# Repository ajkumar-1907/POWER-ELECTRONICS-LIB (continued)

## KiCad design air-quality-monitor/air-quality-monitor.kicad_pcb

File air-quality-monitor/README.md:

# IoT Air Quality Monitoring System

A battery-powered, Wi-Fi connected air-quality monitor built around an **ESP-12E (ESP8266)** and an **MQ-135** gas sensor. It reads gas concentration, shows it on an SSD1306 OLED, and can send the data over Wi-Fi. The board has its own USB-C programming interface, a Li-ion charger and power regulation.

### 3D views

### Layer views

| Front copper | Back copper |
|---|---|
|  |  |
| **Front silkscreen** | **Back silkscreen** |
|  |  |

## Overview

The board combines six functional blocks on one 2-layer PCB:

| Block | Parts | Function |
|---|---|---|
| **USB-to-UART** | USB-C (J23), CH340C (U7), SS8050 ×2 (Q3, Q4) | Programming and serial monitor over USB-C, with ESP auto-reset/flash |
| **MCU** | ESP-12E (U1), RST and FLASH buttons | Wi-Fi microcontroller; reads the sensor and drives the display |
| **Gas sensor** | MQ-135 (U2) + load/divider resistors | Analog gas reading into the ESP8266 ADC (A0) |
| **Display** | 4-pin header (J2) | SSD1306 128×64 I²C OLED (GND / 5V / SCL / SDA) |
| **Battery charging** | TP4056 (U5), status LEDs D1/D2 | Single-cell Li-ion charging from USB |
| **Power supply** | MT3608 boost (U4) + AMS1117-3.3 (U6) | Battery → 5 V (sensor heater, OLED) → 3.3 V (ESP-12E) |

## Working Principle

1. **Power path:** USB-C supplies 5 V. The CC pins have 5.1 kΩ pull-downs (R6, R7), so a USB-C host provides power, and TVS diodes (D6, D7, D9) protect the USB lines. The TP4056 charges the Li-ion cell on J1 at about 1 A (set by R13 = 1.2 kΩ). The red and green LEDs show charging and done.
2. **5 V rail:** the MT3608 boosts the battery voltage (3.0–4.2 V) to 5 V through L1 and Schottky diode D10. USB 5 V is OR-ed onto the same rail through D8 (SS34), so the board runs from USB or from battery.
3. **3.3 V rail:** the AMS1117-3.3 LDO powers the ESP-12E from the 5 V rail.
4. **Sensing:** the MQ-135's heater runs from 5 V. Its sensing element forms a divider with the load resistors, and the scaled voltage goes to the ESP8266's ADC pin. The resistance falls as pollutant gas concentration rises (NH₃, NOₓ, alcohol, benzene, smoke, CO₂).
5. **Programming:** the CH340C converts USB to UART. Its DTR and RTS lines drive the classic two-transistor (Q3, Q4) circuit that pulls the ESP's RESET and GPIO0, so uploads from the Arduino IDE or esptool need no button presses. Manual RST and FLASH buttons are also provided.
6. **Display and I/O:** the OLED connects over I²C (SDA/SCL on J2). D3 is a status LED on GPIO14.

## Key Equations

**TP4056 charge current:**
```
I_charge = 1200 / R_PROG = 1200 / 1.2 kΩ ≈ 1 A
```

**MT3608 boost output (V_FB = 0.6 V):**
```
Vout = 0.6 V × (1 + R_top / R_bottom)      for 5 V: R_top / R_bottom ≈ 7.33
```

**MQ-135 sensor resistance from the measured voltage:**
```
Rs = R_L × (Vc − V_out) / V_out          ppm ≈ a × (Rs / R0)^b   (calibrated curve)
```

**ESP8266 ADC input (0–1 V full scale on ESP-12E A0):**
```
V_ADC = V_sensor × R_bottom / (R_top + R_bottom)   →  must stay ≤ 1.0 V
```

## Typical Applications

- Indoor air-quality monitoring for homes, classrooms and offices
- Kitchen and garage smoke or gas alerts
- IoT dashboards (Blynk, ThingSpeak, MQTT / Home Assistant)
- Learning platform for ESP8266, sensors and battery-powered design

## Specifications (this design)

| Parameter | Value |
|---|---|
| MCU | ESP-12E (ESP8266, 2.4 GHz Wi-Fi) |
| Sensor | MQ-135 (analog) |
| Display | SSD1306 128×64 OLED, I²C |
| Power Input | USB-C 5 V |
| Battery | 1-cell Li-ion / Li-Po (JST-PH 2-pin), 1 A charging |
| Rails | 5 V (MT3608 boost / USB) and 3.3 V (AMS1117) |
| USB-UART | CH340C with auto-reset / auto-flash |
| Board Size | 68 × 47.4 mm, 2-layer, antenna keep-out cut-out |

## Bill of Materials

The full BOM is in [`bom.csv`](bom.csv). The main parts are:

| Ref | Value | Package |
|---|---|---|
| U1 | ESP-12E | Module |
| U2 | MQ-135 gas sensor | 6-pin |
| U4 | MT3608 boost converter | SOT-23-6 |
| U5 | TP4056 Li-ion charger | ESOP-8 |
| U6 | AMS1117-3.3 LDO | SOT-223 |
| U7 | CH340C USB-UART | SOIC-16 |
| Q3, Q4 | SS8050 NPN | SOT-23 |
| D8, D10 | SS34 Schottky | SMA |
| D6, D7, D9 | LESD5D5.0CT1G TVS | SOD-523 |
| J23 | USB-C receptacle, 16-pin | SMD |
| J1 / J2 / J3 | JST-PH battery / OLED header / 3-pin header | THT |

## Design Notes

- **MT3608 parts not specified.** R1, R2 (feedback divider) and L1 are left as "R" and "L" in the schematic. Pick R_top / R_bottom ≈ 7.33 for 5 V (for example 22 kΩ / 3 kΩ) and a 22 µH power inductor rated above about 2 A before ordering.
- **ADC range.** The ESP-12E's A0 pin reads 0–1 V. Check that the sensor divider keeps the maximum reading under 1 V.
- **Sensor warm-up and power.** The MQ-135 heater draws about 150 mA at 5 V and needs a 24–48 h burn-in plus calibration (R0 in clean air) before readings are meaningful. On battery it is the dominant load, so consider duty-cycling the heater or deep sleep for long runtime.
- **Antenna.** Keep the cut-out and keep-out zone under the ESP-12E antenna free of copper and components for good Wi-Fi range.
- **Firmware** isn't included in this folder. The 3D models used for the renders (OLED, sensor, USB-C, etc.) aren't included either; KiCad shows those parts without a 3D body.

## Pros & Cons

**Pros:**
- All-in-one: MCU, sensor, display, charger and programmer on a single board
- USB-C with ESD protection and one-click auto-flash
- Runs from USB or battery (power OR-ing)
- Wi-Fi connectivity for cloud dashboards

**Cons:**
- MQ-135 is a low-cost, broad-spectrum sensor: it is not selective and needs calibration
- The heater current limits battery life
- The AMS1117 LDO is inefficient from 5 V
- The ESP8266 has only one ADC channel (0–1 V)

## Files in This Folder

| File | Description |
|---|---|
| `air-quality-monitor.kicad_pro` | KiCad project file |
| `air-quality-monitor.kicad_sch` | Schematic source file |
| `air-quality-monitor.kicad_pcb` | PCB layout source file |
| `air-quality-monitor-PTH.drl` | Plated through-hole drill file (incl. USB-C shell slots) |
| `air-quality-monitor-NPTH.drl` | Non-plated drill file |
| `gerbers/` | Gerber files for fabrication (incl. paste layers for stencil) |
| `bom.csv` | Bill of materials |
| `schematic.png` | Schematic image |
| `pcb-layout2.png` | PCB layout preview (KiCad editor view) |
| `pcb-layout.png` | PCB top and bottom render from the Gerbers |
| `pcb-front-copper.png` / `pcb-back-copper.png` | Copper layer views |
| `pcb-front-silkscreen.png` / `pcb-back-silkscreen.png` | Silkscreen layer views |
| `pcb-3d-top.png` / `pcb-3d-bottom.png` / `pcb-3d-angle.png` | 3D renders |

## How to Use

1. Clone or download this repository.
2. Open `air-quality-monitor.kicad_pro` in [KiCad](https://www.kicad.org/) (v10 or later).
3. Set values for R1, R2 and L1 (see Design Notes), then order the PCB: zip the contents of `gerbers/` together with the two `.drl` files and upload them to any fab.
4. After assembly, plug in USB-C. The board shows up as a CH340 COM port. Flash it from the Arduino IDE (board: *NodeMCU 1.0 (ESP-12E)*) or with esptool.
5. Connect the OLED to J2 and a 1-cell Li-ion battery to J1, then let the MQ-135 burn in before calibrating.

## License

Released under the [MIT License](../LICENSE).

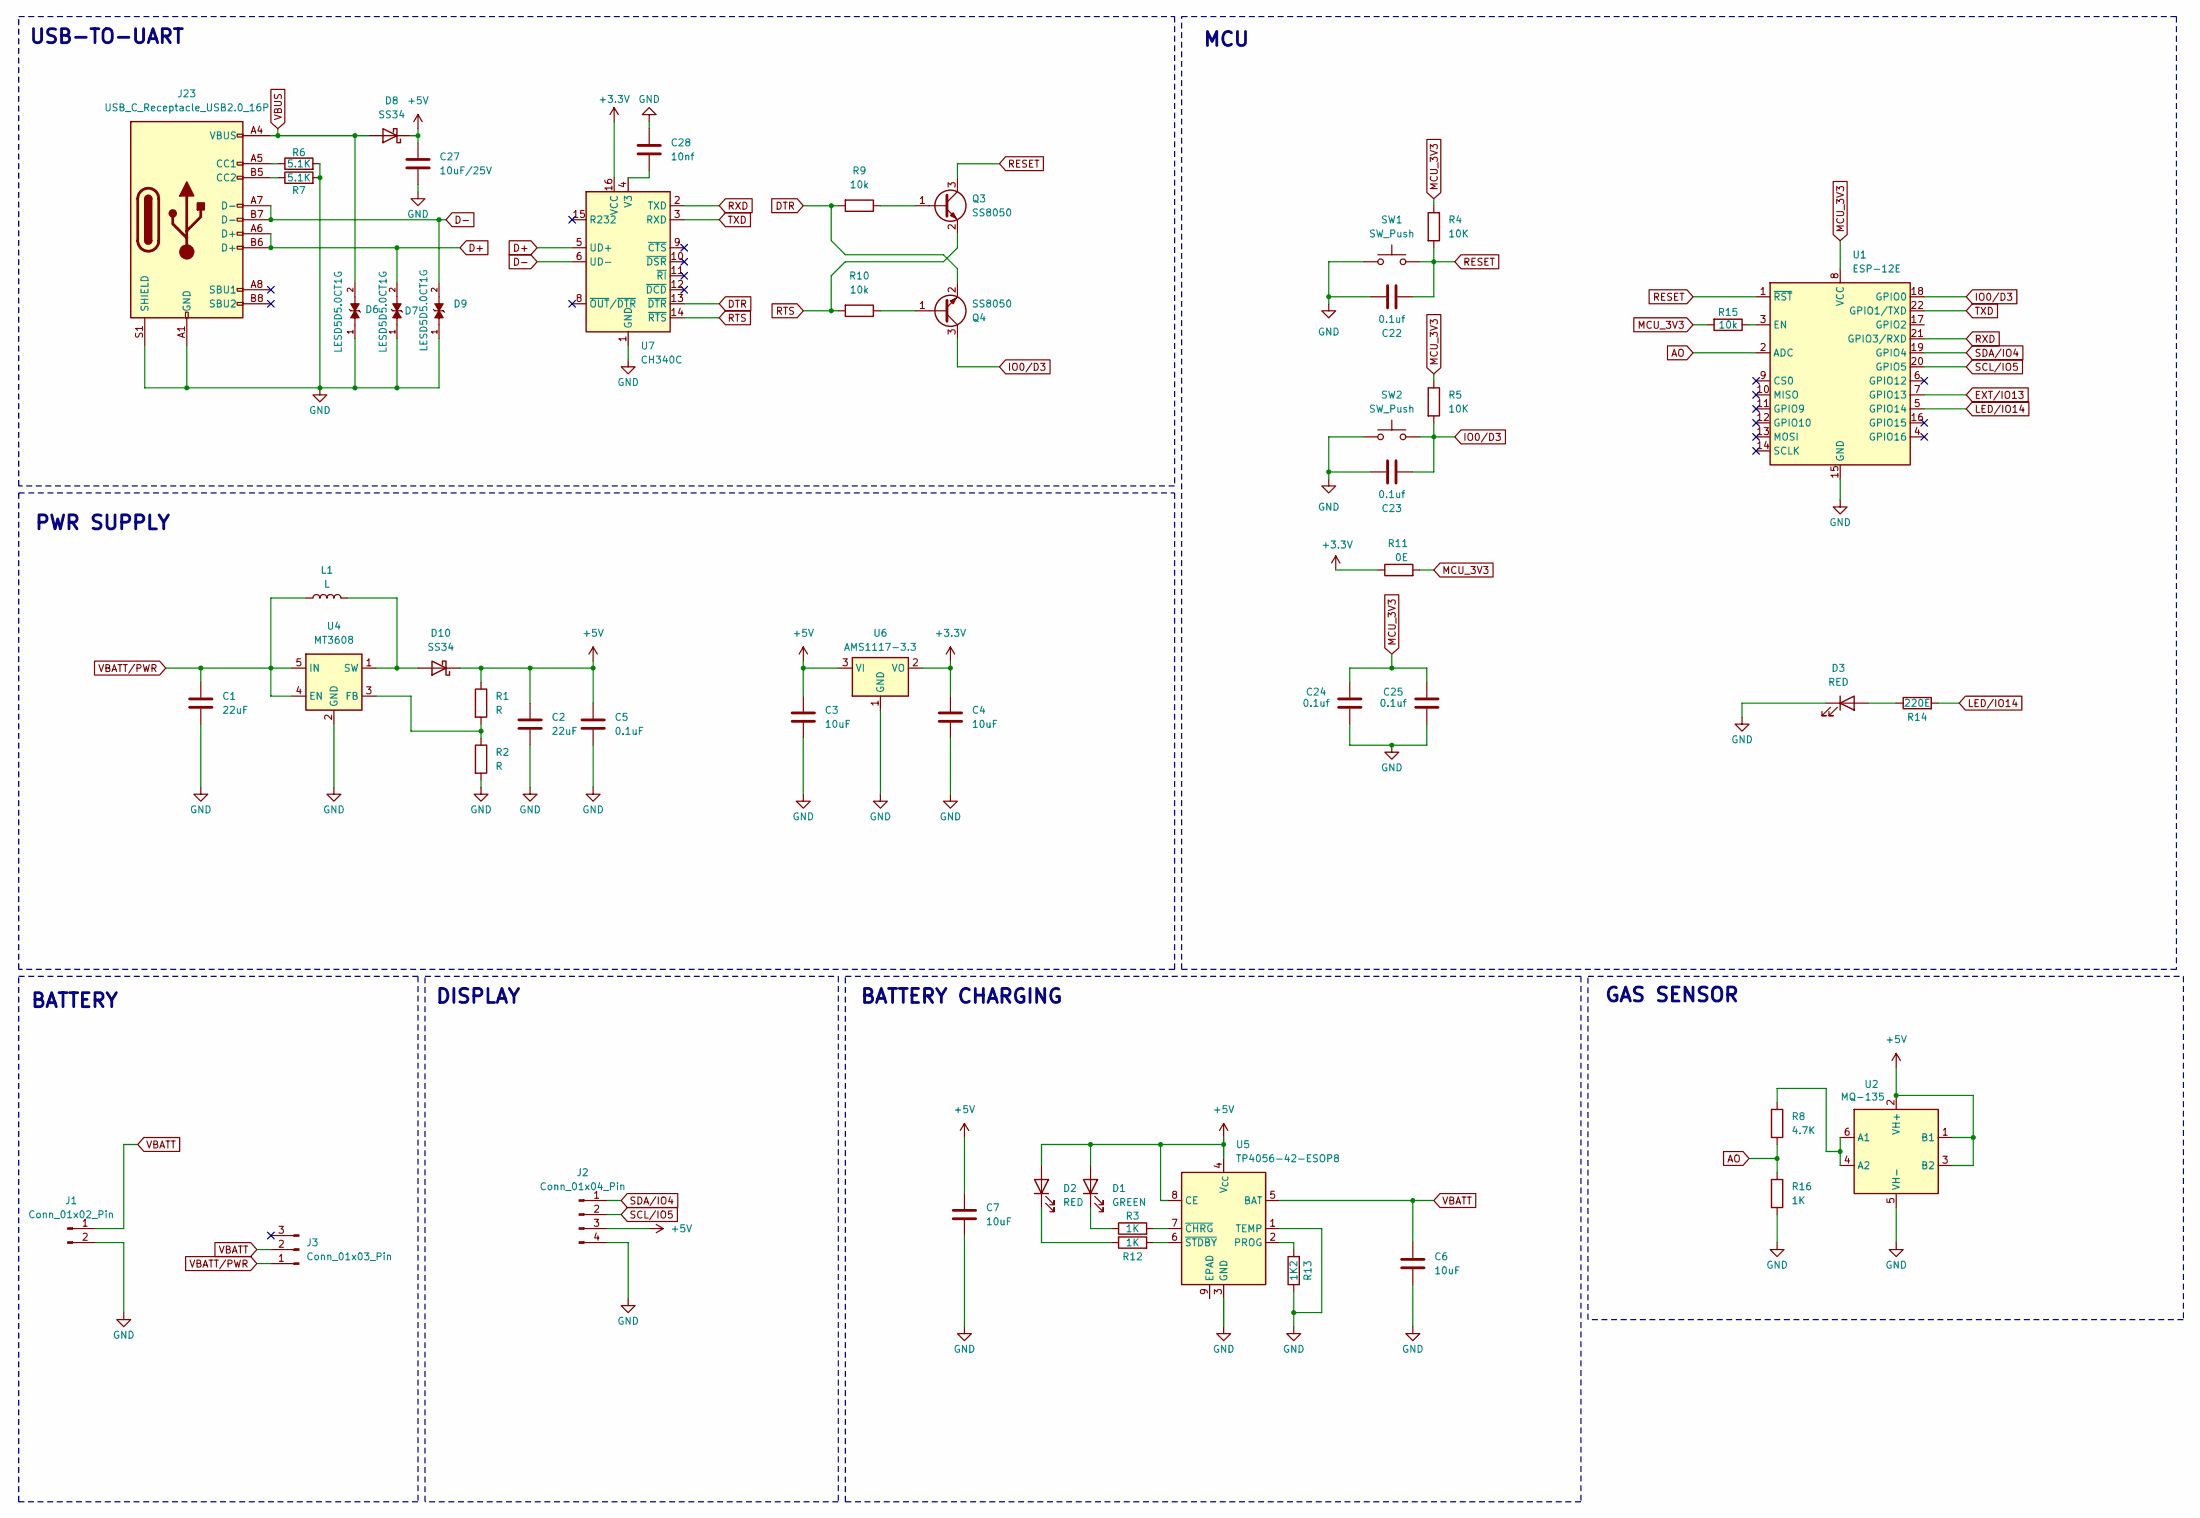
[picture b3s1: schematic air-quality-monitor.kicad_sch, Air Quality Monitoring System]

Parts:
C1, C2: 22uF; C_1206_3216Metric
C3, C4, C6, C7: 10uF; C_1206_3216Metric
C5: 0.1uF; C_0603_1608Metric
C22, C23, C24, C25: 0.1uf; C_0603_1608Metric
C27: 10uF/25V; C_1206_3216Metric
C28: 10nf; C_0603_1608Metric
D1: GREEN; LED_0603_1608Metric
D2, D3: RED; LED_0603_1608Metric
D6, D7, D9: LESD5D5.0CT1G; TVS_LESD5D5.0CT1G; PARTREV O
D8, D10: SS34; D_SMA
J1: Conn_01x02_Pin; JST_PH_S2B-PH-K_1x02_P2.00mm_Horizontal
J2: Conn_01x04_Pin; PinSocket_1x04_P2.54mm_Vertical
J3: Conn_01x03_Pin; PinHeader_1x03_P2.54mm_Vertical
J23: USB_C_Receptacle_USB2.0_16P; USB_C_Receptacle_HCTL_HC-TYPE-C-16P-01A
L1: L; L_10.4x10.4_H4.8
Q3, Q4: SS8050; SOT-23
R1, R2: R; R_1206_3216Metric
R3, R12, R16: 1K; R_1206_3216Metric
R4, R5: 10K; R_1206_3216Metric
R6, R7: 5.1K; R_0603_1608Metric
R8: 4.7K; R_1206_3216Metric
R9, R10: 10k; R_0603_1608Metric
R11: 0E; R_0603_1608Metric
R13: 1K2; R_1206_3216Metric
R14: 220E; R_1206_3216Metric
R15: 10k; R_1206_3216Metric
SW1, SW2: SW_Push; SW_Push_SPST_NO_Alps_SKRK
U1: ESP-12E
U2: MQ-135; MQ-6
U4: MT3608; SOT-23-6
U5: TP4056-42-ESOP8; SOIC-8-1EP_3.9x4.9mm_P1.27mm_EP2.41x3.3mm_ThermalVias
U6: AMS1117-3.3; SOT-223-3_TabPin2
U7: CH340C; SOIC-16_3.9x9.9mm_P1.27mm

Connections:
+3.3V: C4.1, R11.1, U6.2 (VO), U7.16 (VCC)
+5V: C2.1, C3.1, C5.1, C7.1, C27.1, D1.2 (A), D2.2 (A), D8.1 (K), D10.1 (K), J2.3, R1.1, U2.1 (B1), U2.2 (VH+), U2.3 (B2), U5.4 (V_{CC}), U5.8 (CE), U6.3 (VI)
AO: R8.2, R16.1, U1.2 (ADC)
D+: D7.2, J23.A6 (D+), J23.B6 (D+), U7.5 (UD+)
D-: D9.2, J23.A7 (D-), J23.B7 (D-), U7.6 (UD-)
DTR: Q4.2 (E), R9.2, U7.13 (~DTR)
EXT/IO13: U1.7 (GPIO13)
GND: C1.2, C2.2, C3.2, C4.2, C5.2, C6.2, C7.2, C22.1, C23.1, C24.1, C25.1, C27.2, C28.1, D3.1 (K), D6.1, D7.1, D9.1, J1.2, J2.4, J23.A1 (GND), J23.A12 (GND), J23.B1 (GND), J23.B12 (GND), J23.S1 (SHIELD), R2.2, R6.2, R7.2, R13.1, R16.2, SW1.1, SW2.1, U1.15 (GND), U2.5 (VH-), U4.2 (GND), U5.1 (TEMP), U5.3 (GND), U6.1 (GND), U7.1 (GND)
IO0/D3: C23.2, Q4.3 (C), R5.2, SW2.2, U1.18 (GPIO0)
LED/IO14: R14.2, U1.5 (GPIO14)
MCU_3V3: C24.2, C25.2, R4.1, R5.1, R11.2, R15.2, U1.8 (VCC)
unnamed: D1.1 (K), R3.1
unnamed: D2.1 (K), R12.1
unnamed: D3.2 (A), R14.1
unnamed: D10.2 (A), L1.2, U4.1 (SW)
unnamed: J23.A5 (CC1), R6.1
unnamed: J23.B5 (CC2), R7.1
unnamed: Q3.1 (B), R9.1
unnamed: Q4.1 (B), R10.1
unnamed: R15.1, U1.3 (EN)
unnamed: R8.1, U2.4 (A2), U2.6 (A1)
unnamed: R1.2, R2.1, U4.3 (FB)
unnamed: R13.2, U5.2 (PROG)
unnamed: R3.2, U5.7 (~CHRG)
unnamed: R12.2, U5.6 (~STDBY)
unnamed: C28.2, U7.4 (V3)
RESET: C22.2, Q3.3 (C), R4.2, SW1.2, U1.1 (~RST)
RTS: Q3.2 (E), R10.2, U7.14 (~RTS)
RXD: U1.21 (GPIO3/RXD), U7.2 (TXD)
SCL/IO5: J2.2, U1.20 (GPIO5)
SDA/IO4: J2.1, U1.19 (GPIO4)
TXD: U1.22 (GPIO1/TXD), U7.3 (RXD)
VBATT: C6.1, J1.1, J3.2, U5.5 (BAT)
VBATT/PWR: C1.1, J3.1, L1.1, U4.4 (EN), U4.5 (IN)
VBUS: D6.2, D8.2 (A), J23.A4 (VBUS), J23.A9 (VBUS), J23.B4 (VBUS), J23.B9 (VBUS)

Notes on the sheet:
PWR SUPPLY
USB-TO-UART
DISPLAY
GAS SENSOR
BATTERY CHARGING
MCU
BATTERY

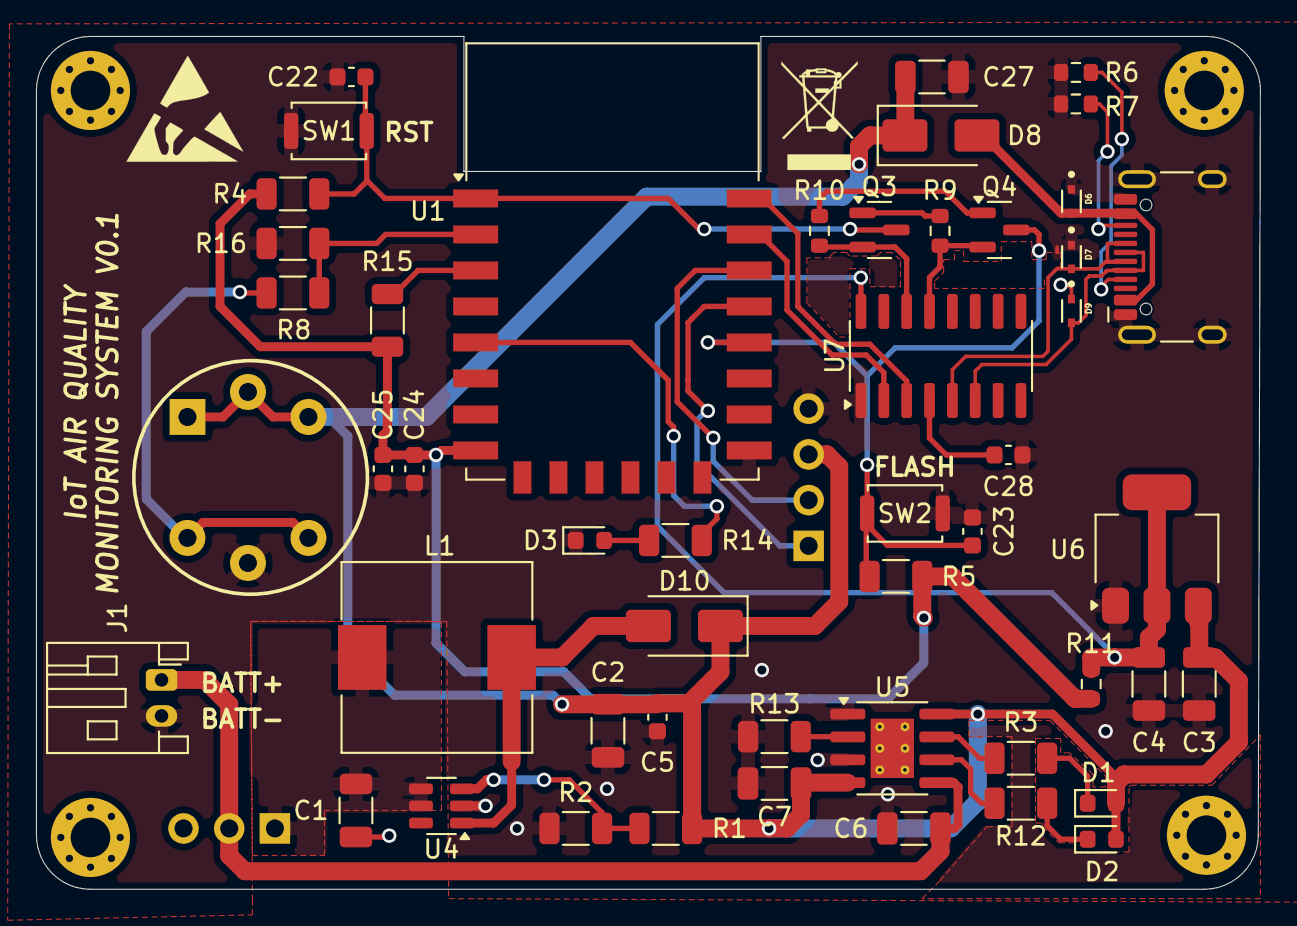
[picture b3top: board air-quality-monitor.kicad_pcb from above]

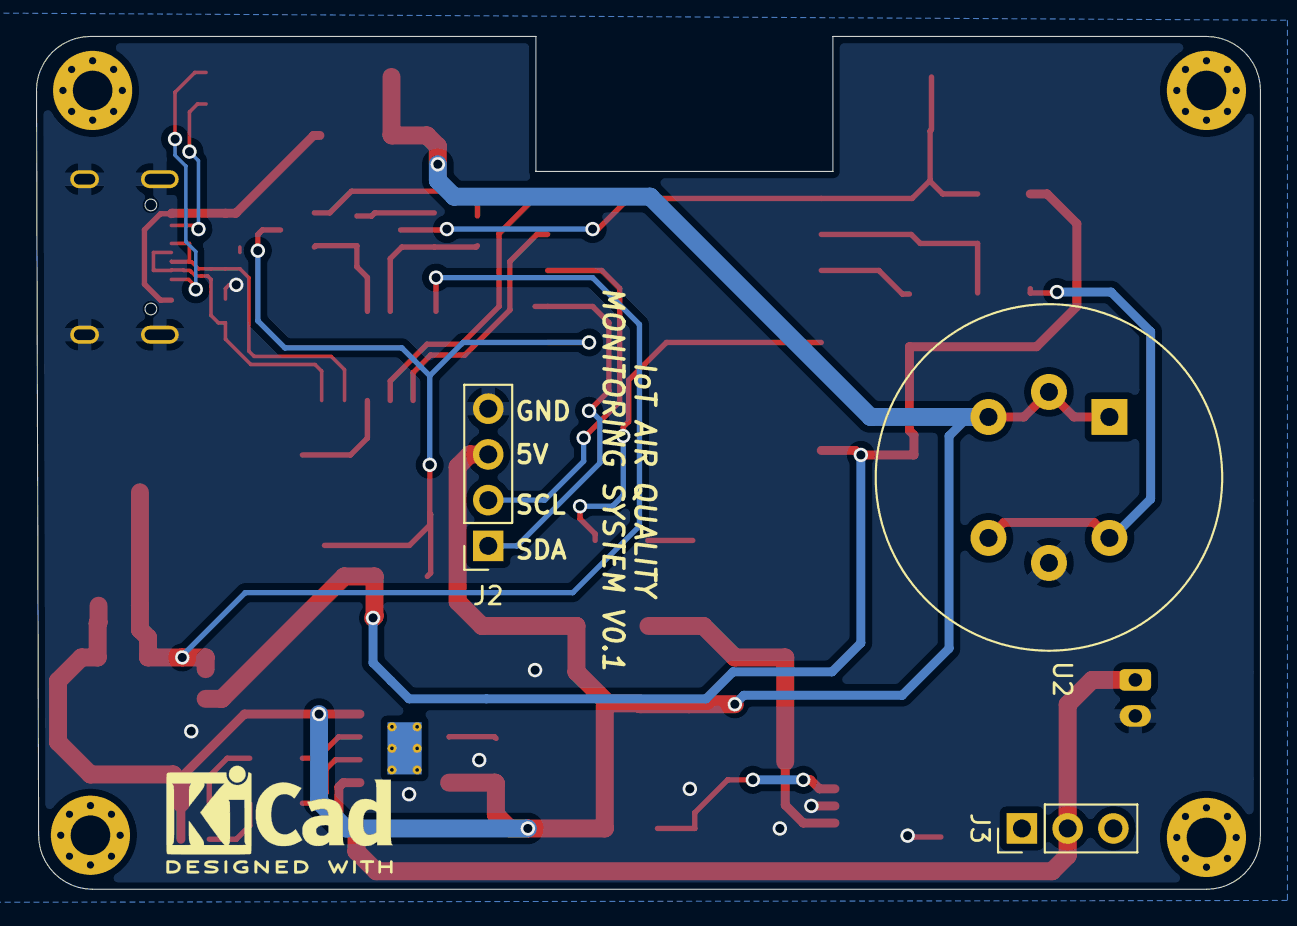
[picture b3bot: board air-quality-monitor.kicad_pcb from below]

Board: 2 copper layers, 68.0 x 47.4 mm, 56 parts (3 on the bottom side), 34 nets.

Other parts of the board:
REFe: MountingHole_2.2mm_M2_Pad_Via
REFe#2, REFe#3, REFe#4: MountingHole_2.2mm_M2_Pad_Via

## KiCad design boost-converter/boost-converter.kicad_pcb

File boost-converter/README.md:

# Boost Converter (XL6009)

An adjustable step-up DC-DC converter built around the **XL6009** switching regulator. It raises a lower DC input to a higher, regulated DC output, which you set with a multi-turn trimmer.

## Overview

The boost converter is the basic step-up switch-mode topology. Energy is stored in an inductor while a switch is on, then released to the output, on top of the input voltage, while the switch is off. The XL6009 integrates the power switch (4 A), oscillator (400 kHz) and control loop, so the design needs only an inductor, a Schottky diode, capacitors and a feedback divider.

## Working Principle

1. **Switch ON:** the XL6009's internal switch connects the SW node (the end of L1) to GND. Input current ramps up through L1, storing energy in its magnetic field. D1 is reverse-biased, so C4 supplies the load.
2. **Switch OFF:** the switch opens. L1 keeps its current flowing, which forces the SW node above the input voltage. D1 (SS34 Schottky) conducts and delivers energy to C4 and the load.
3. **Regulation:** the output is divided down by RV1 (50 kΩ trimmer) and R1 (1 kΩ) into the FB pin. The XL6009 adjusts its duty cycle to hold FB at 1.25 V.
4. **Filtering:** C1 (47 µF) and C2 (1 µF) decouple the input, and C4 (220 µF) and C3 (1 µF) smooth the output.
5. **Enable:** the EN pin is left unconnected. On the XL6009 a floating EN defaults high, so the converter is always on.

## Key Equations

**Output voltage (feedback divider, V_FB = 1.25 V):**
```
Vout = 1.25 V × (1 + RV1 / R1)
     = 1.25 × (1 + 0…50k / 1k)  →  set range ≈ Vin … 63 V (see Design Notes)
```

**Duty cycle (continuous conduction mode):**
```
D = 1 − Vin / Vout          e.g. 12 V → 24 V : D = 0.5
```

**Inductor ripple current:**
```
ΔI_L = Vin × D / (L × f) = 12 × 0.5 / (33 µH × 400 kHz) ≈ 0.45 A
```

**Output voltage ripple (capacitive part):**
```
ΔVout ≈ Iout × D / (f × C4) = 1 A × 0.5 / (400 kHz × 220 µF) ≈ 6 mV
```

**Input current (power balance):**
```
Iin ≈ (Vout × Iout) / (Vin × η)      η ≈ 85–94 %
```

## Typical Applications

- Running 12 V / 19 V / 24 V devices from a 5 V USB or single Li-ion supply
- Laptop chargers in the car (12 V → 19 V)
- Solar and battery systems that need a higher bus voltage
- Bench supply for testing high-voltage LEDs, motors and other loads

## Specifications (this design)

| Parameter | Value |
|---|---|
| Input Voltage | 5–32 V DC (XL6009 range) |
| Output Voltage | Adjustable, Vin to ~35 V (XL6009 / SS34 limit) |
| Switch Current | 4 A peak (internal switch) |
| Switching Frequency | 400 kHz (fixed) |
| Feedback Reference | 1.25 V |
| Board Size | 45 × 20 mm, 2-layer, thermal-via array under VR1 |

## Bill of Materials

| Ref | Value | Package | Qty |
|---|---|---|---|
| VR1 | XL6009 boost regulator | TO-263-5 | 1 |
| L1 | 33 µH power inductor (CDRH127-type, 12 × 12 mm) | SMD | 1 |
| D1 | SS34 Schottky diode (40 V, 3 A) | SMA | 1 |
| C1 | 47 µF / 50 V electrolytic | Radial D6.3 mm | 1 |
| C4 | 220 µF / 50 V electrolytic | Radial D6.3 mm | 1 |
| C2, C3 | 1 µF ceramic | 0805 | 2 |
| R1 | 1 kΩ | 1206 | 1 |
| RV1 | 50 kΩ multi-turn trimmer | Bourns 3296W | 1 |
| J1–J4 | IN+ / IN− / OUT+ / OUT− pads | 2.54 mm pin | 4 |

## Design Notes

- **The trimmer can ask for more voltage than the parts can handle.** With R1 = 1 kΩ and RV1 = 50 kΩ, the feedback divider can request up to about 63 V. The XL6009 is specified up to ~35 V output, the SS34 is rated at 40 V and the capacitors at 50 V. **Set the voltage with no load and a meter connected, turning the trimmer slowly.** To limit the range in hardware, change R1 to 2 kΩ, which caps Vout at about 32.5 V.
- **A boost converter can't go below Vin.** When the switch is off, the input connects straight to the output through L1 and D1. Vout is always at least about Vin − 0.4 V, and there's no short-circuit protection on the output.
- **Thermal design.** VR1's tab sits on a large array of thermal vias into a bottom copper pour. Above ~1.5 A input current, add airflow or a heatsink.
- **Layout.** Keep the SW node (L1 / D1 / VR1 pin 3) loop small, as this layout does, to minimise switching noise.

## Pros & Cons

**Pros:**
- Simple topology with few components and an integrated 4 A switch
- High efficiency (typically 85–94 %)
- Wide adjustable output range with a 25-turn trimmer
- The 400 kHz switching frequency allows a small inductor and capacitors

**Cons:**
- Non-isolated (output shares ground with the input)
- No current limiting or short-circuit protection at the output
- Input current is higher than output current; the source must supply Iin ≈ Vout·Iout / (Vin·η)
- The trimmer range exceeds the part ratings unless R1 is changed (see Design Notes)

## Files in This Folder

| File | Description |
|---|---|
| `boost-converter.kicad_pro` | KiCad project file |
| `boost-converter.kicad_sch` | Schematic source file |
| `boost-converter.kicad_pcb` | PCB layout source file |
| `boost-converter-PTH.drl` | Plated through-hole drill file |
| `boost-converter-NPTH.drl` | Non-plated through-hole drill file |
| `gerbers/` | Gerber files for fabrication |
| `schematic.png` | Schematic preview image |
| `pcb-layout2.png` | PCB layout preview (KiCad editor view) |
| `pcb-layout.png` | PCB top and bottom render from the Gerbers |
| `pcb-3d-top.png` | 3D render, top side |
| `pcb-3d-bottom.png` | 3D render, bottom side |

## How to Use

1. Clone or download this repository.
2. Open `boost-converter.kicad_pro` in [KiCad](https://www.kicad.org/) (v10 or later).
3. To manufacture, zip the contents of `gerbers/` together with the two `.drl` files and upload them to any PCB fab.
4. After assembly, connect the supply to **IN+ / IN−**. With no load attached and a multimeter on **OUT+ / OUT−**, turn RV1 until you reach the voltage you need, then connect the load.

## License

Released under the [MIT License](../LICENSE).

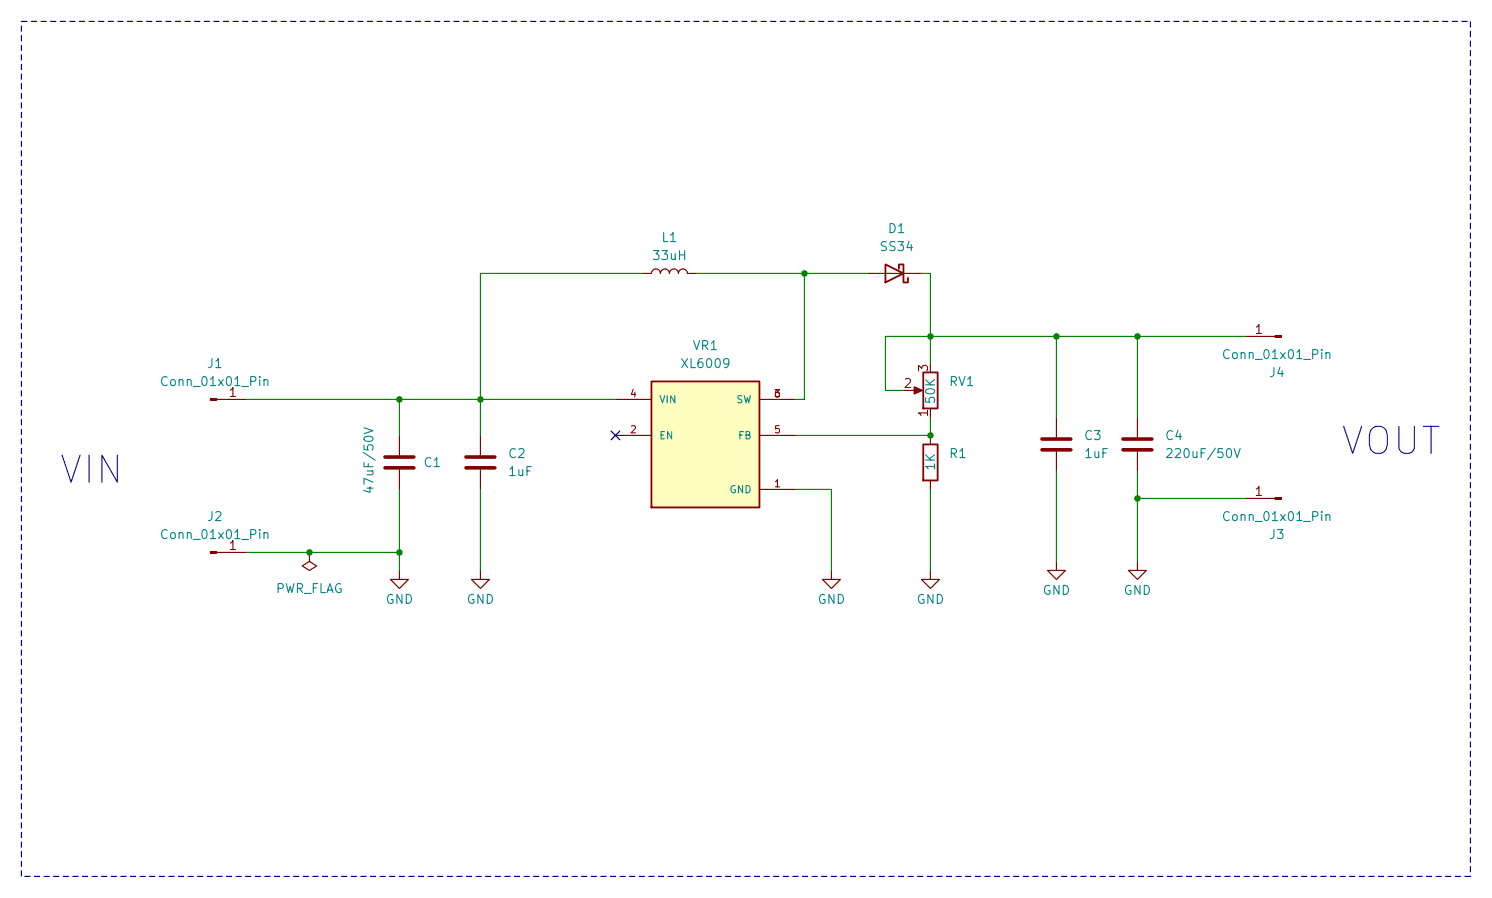
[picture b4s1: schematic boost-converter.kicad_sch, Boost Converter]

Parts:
C1: 47uF/50V; C_Radial_D6.3mm_H11.0mm_P2.50mm
C2, C3: 1uF; C_0805_2012Metric
C4: 220uF/50V; C_Radial_D6.3mm_H11.0mm_P2.50mm
D1: SS34; D_SMA
J1, J2, J3, J4: Conn_01x01_Pin; PinHeader_1x01_P2.54mm_Vertical
L1: 33uH; L_12x12mm_H8mm
R1: 1K; R_1206_3216Metric
RV1: 50K; Potentiometer_Bourns_3296W_Vertical
VR1: XL6009; PARTREV 1.1

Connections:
GND: C1.2, C2.2, C3.2, C4.2, J2.1, J3.1, R1.2, VR1.1 (GND)
unnamed: D1.2 (A), L1.2, VR1.3 (SW), VR1.6 (SW)
unnamed: C3.1, C4.1, D1.1 (K), J4.1, RV1.2, RV1.3
unnamed: C1.1, C2.1, J1.1, L1.1, VR1.4 (VIN)
unnamed: R1.1, RV1.1, VR1.5 (FB)

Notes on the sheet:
VIN
VOUT

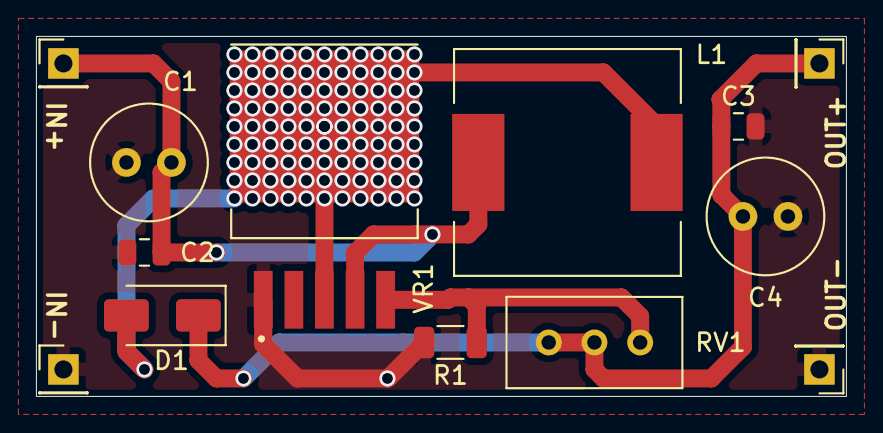
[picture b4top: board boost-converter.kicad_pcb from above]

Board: 2 copper layers, 45.0 x 20.0 mm, 13 parts (0 on the bottom side), 5 nets.

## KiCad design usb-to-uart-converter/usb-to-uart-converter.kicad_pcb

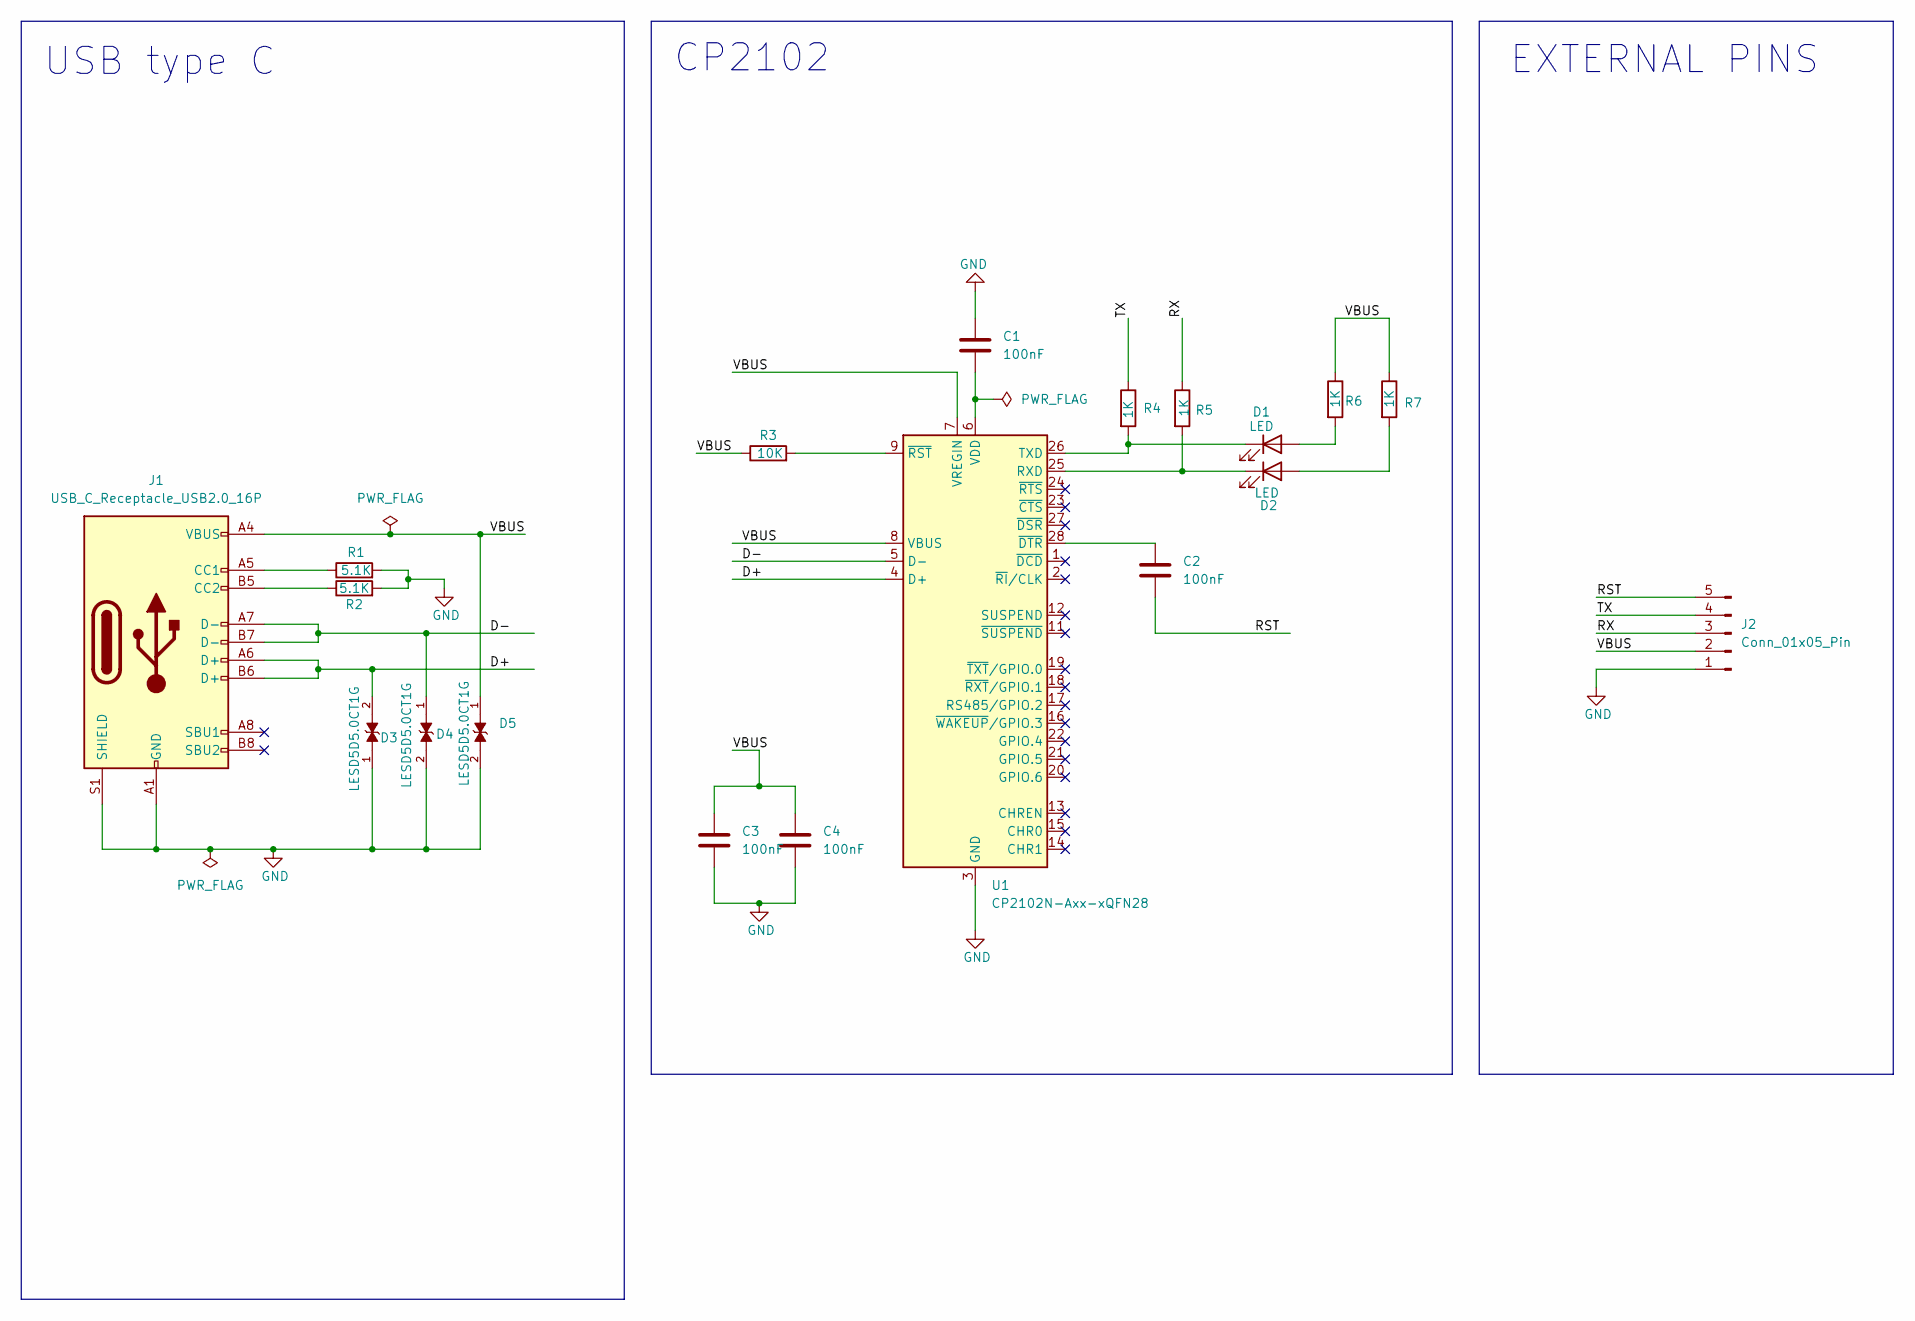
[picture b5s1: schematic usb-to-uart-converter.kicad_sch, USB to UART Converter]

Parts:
C1, C2, C3, C4: 100nF; C_0201_0603Metric
D1, D2: LED; LED_0201_0603Metric
D3, D4, D5: LESD5D5.0CT1G; TVS_LESD5D5.0CT1G; PARTREV O
J1: USB_C_Receptacle_USB2.0_16P; USB_C_Receptacle_HRO_TYPE-C-31-M-12
J2: Conn_01x05_Pin; PinHeader_1x05_P2.54mm_Horizontal
R1, R2: 5.1K; R_0201_0603Metric
R3: 10K; R_0201_0603Metric
R4, R5, R6, R7: 1K; R_0201_0603Metric
U1: CP2102N-Axx-xQFN28; QFN-28-1EP_5x5mm_P0.5mm_EP3.35x3.35mm

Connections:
/D+: D3.2, J1.A6 (D+), J1.B6 (D+), U1.4 (D+)
/D-: D4.1, J1.A7 (D-), J1.B7 (D-), U1.5 (D-)
/RST: C2.1, J2.5
/RX: J2.3, R5.1
/TX: J2.4, R4.1
/VBUS: C3.1, C4.1, D5.1, J1.A4 (VBUS), J1.A9 (VBUS), J1.B4 (VBUS), J1.B9 (VBUS), J2.2, R3.1, R6.1, R7.1, U1.7 (VREGIN), U1.8 (VBUS)
GND: C1.1, C3.2, C4.2, D3.1, D4.2, D5.2, J1.A1 (GND), J1.A12 (GND), J1.B1 (GND), J1.B12 (GND), J1.S1 (SHIELD), J2.1, R1.2, R2.2, U1.3 (GND), U1.29 (GND)
unnamed: D1.2 (A), R6.2
unnamed: D1.1 (K), R4.2, U1.26 (TXD)
unnamed: D2.2 (A), R7.2
unnamed: D2.1 (K), R5.2, U1.25 (RXD)
unnamed: J1.A5 (CC1), R1.1
unnamed: J1.B5 (CC2), R2.1
unnamed: C1.2, U1.6 (VDD)
unnamed: C2.2, U1.28 (~DTR)
unnamed: R3.2, U1.9 (~RST)

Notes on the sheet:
CP2102
USB type C
EXTERNAL PINS

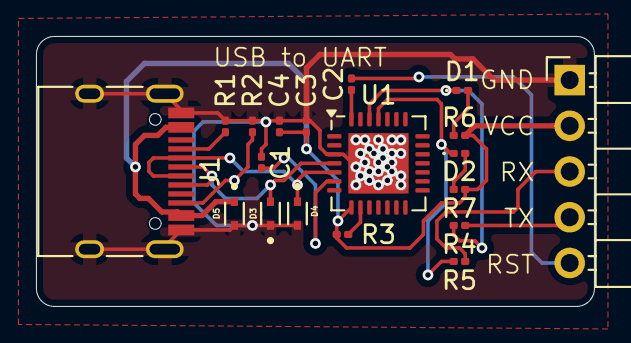
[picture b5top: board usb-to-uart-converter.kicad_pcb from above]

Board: 2 copper layers, 31.0 x 15.0 mm, 19 parts (0 on the bottom side), 16 nets.

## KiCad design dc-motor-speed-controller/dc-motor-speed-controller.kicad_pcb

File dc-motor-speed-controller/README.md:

# DC Motor Speed Controller (555 PWM)

A PWM speed controller for brushed DC motors. An NE555 timer generates a fixed-frequency PWM signal whose duty cycle is set by a potentiometer, and a TIP122 Darlington transistor switches the motor current.

## Overview

Reducing a DC motor's supply with a series resistor wastes power as heat and kills low-speed torque. **Pulse-width modulation (PWM)** instead switches the motor fully on and fully off many times a second. The motor's inductance and mechanical inertia average the pulses, so the effective voltage is set by the **duty cycle**:

```
V_avg = D × Vin
```

Because the switching transistor is either fully on or fully off, very little power is lost in it, and the motor keeps good torque even at low speed.

## Working Principle

1. **Oscillator:** the NE555 runs in astable mode. Steering diodes D1 and D2 split the potentiometer RV1 into a charge path and a discharge path.
2. **Charging (output HIGH):** C1 charges from VCC through R1, D1 and one side of RV1 (pin 3 to the wiper).
3. **Discharging (output LOW):** C1 discharges through the other side of RV1 (wiper to pin 1) and D2 into the 555's discharge pin (7).
4. **Duty-cycle control:** turning RV1 moves resistance from one path to the other. This changes the duty cycle while the **total period stays almost constant**, so speed changes without the frequency drifting.
5. **Power stage:** the 555 output drives the TIP122's base through R2 (1 kΩ). The TIP122 switches the motor's low side; the motor sits between VCC (J2 +) and the collector (J2 −).
6. **Flyback protection:** D3 is across the motor and clamps the inductive voltage spike when the transistor turns off.
7. **Supply and indicator:** C3 (1000 µF) is the bulk decoupling capacitor and absorbs motor current spikes. C2 (100 nF) stabilises the 555's control-voltage pin, and D4 lights through R3 (2.2 kΩ) when power is on.

## Key Equations

**PWM period and frequency (independent of pot position):**
```
T ≈ 0.693 × (R1 + RV1) × C1 = 0.693 × 101 kΩ × 100 nF ≈ 7 ms
f ≈ 1 / T ≈ 143 Hz
```

**Duty cycle (Ra = charge-side part of RV1):**
```
D ≈ (R1 + Ra) / (R1 + RV1)      →  ≈ 1 % … 99 %
```

**Average motor voltage:**
```
V_motor ≈ D × (Vin − V_CE(sat))      V_CE(sat) of TIP122 ≈ 1–2 V
```

**TIP122 base current (12 V supply):**
```
I_B ≈ (V_OH − 2 × V_BE) / R2 ≈ (10.5 − 1.4) / 1k ≈ 9 mA
I_C(max) ≈ h_FE × I_B ≫ motor current   (h_FE ≥ 1000)
```

**Transistor dissipation (sets heatsink need):**
```
P_Q1 ≈ V_CE(sat) × I_motor × D
```

## Typical Applications

- Speed control for 12 V DC fans, pumps and small gear motors
- DIY drills, grinders and hobby machines
- LED-strip dimming (the same circuit drives resistive loads)
- Robotics and conveyor prototypes

## Specifications (this design)

| Parameter | Value |
|---|---|
| Input Voltage | 5–15 V DC (NE555 limit: 16 V) |
| Output | PWM, low-side switched, ≈ 1–99 % duty |
| PWM Frequency | ≈ 143 Hz |
| Output Current | Up to ~3 A with a heatsink on Q1 (TIP122 rating: 5 A) |
| Board Size | 56.5 × 29 mm, 2-layer, 4 × mounting holes |

## Bill of Materials

| Ref | Value | Package | Qty |
|---|---|---|---|
| U1 | NE555P timer | DIP-8 | 1 |
| Q1 | TIP122 Darlington NPN | TO-220 | 1 |
| RV1 | 100 kΩ potentiometer | Alps RK163, single | 1 |
| R1, R2 | 1 kΩ, ¼ W | Axial DIN0204 | 2 |
| R3 | 2.2 kΩ, ¼ W | Axial DIN0204 | 1 |
| C1, C2 | 100 nF ceramic | Disc, P5 mm | 2 |
| C3 | 1000 µF electrolytic (≥ 25 V) | Radial D10 mm, P5 mm | 1 |
| D1, D2 | 1N4007 (steering) | DO-41 | 2 |
| D3 | 1N4007 (flyback) | DO-41 | 1 |
| D4 | 5 mm LED | THT | 1 |
| J1, J2 | 2-pin screw terminal, 5.08 mm | THT | 2 |

## Design Notes

- **Supply voltage:** the 555 runs directly from the input, so keep Vin ≤ 15 V. For higher-voltage motors (24 V), feed the 555 from a 7812 or a zener-regulated rail.
- **Heatsink:** the TIP122 is a Darlington with a 1–2 V saturation drop, so it dissipates noticeable power. Fit a heatsink on Q1 above about 1 A. For high currents, a logic-level MOSFET (e.g. IRLZ44N) runs much cooler.
- **Flyback diode:** the 1N4007 works at 143 Hz, but a fast or Schottky diode (UF4007, 1N5819) handles the switching edges better.
- **Audible whine:** 143 Hz is within the audible range, so some motors will hum. Lowering C1 to 10 nF moves the PWM to about 1.4 kHz.

## Pros & Cons

**Pros:**
- Efficient compared with resistive or linear speed control
- Keeps good torque at low speed
- Constant frequency across the whole speed range
- Cheap, common, all-through-hole parts

**Cons:**
- One direction only (no H-bridge)
- Open-loop: speed changes with load, because there is no feedback
- The Darlington's saturation drop limits efficiency at high current
- Low PWM frequency can cause audible motor noise

## Files in This Folder

| File | Description |
|---|---|
| `dc-motor-speed-controller.kicad_pro` | KiCad project file |
| `dc-motor-speed-controller.kicad_sch` | Schematic source file |
| `dc-motor-speed-controller.kicad_pcb` | PCB layout source file |
| `dc-motor-speed-controller-PTH.drl` | Plated through-hole drill file |
| `dc-motor-speed-controller-NPTH.drl` | Non-plated through-hole drill file |
| `gerbers/` | Gerber files for fabrication |
| `schematic.png` | Schematic preview image |
| `pcb-layout2.png` | PCB layout preview (KiCad editor view) |
| `pcb-layout.png` | PCB top and bottom render from the Gerbers |
| `pcb-3d-top.png` | 3D render, top side |
| `pcb-3d-bottom.png` | 3D render, bottom side |

## How to Use

1. Clone or download this repository.
2. Open `dc-motor-speed-controller.kicad_pro` in [KiCad](https://www.kicad.org/) (v10 or later).
3. To manufacture, zip the contents of `gerbers/` together with the two `.drl` files and upload them to any PCB fab.
4. After assembly, connect the DC supply to J1 (**DC IN**, + / −) and the motor to J2 (**Output**, + / −). Turn RV1 to set the speed.

## License

Released under the [MIT License](../LICENSE).

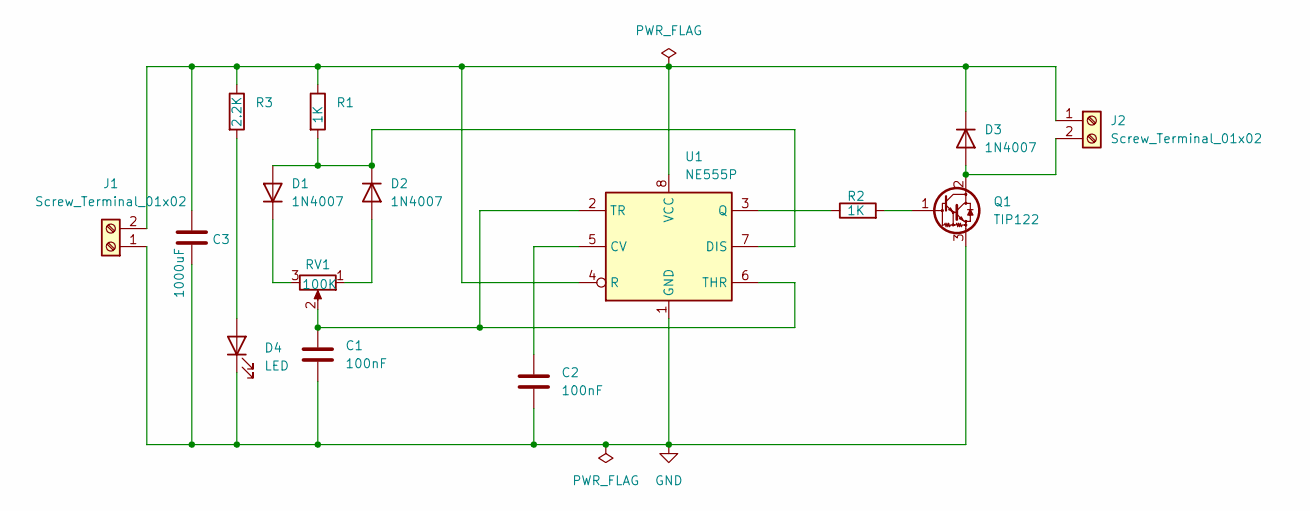
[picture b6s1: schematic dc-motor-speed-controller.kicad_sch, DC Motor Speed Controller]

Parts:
C1, C2: 100nF; C_Disc_D4.7mm_W2.5mm_P5.00mm
C3: 1000uF; CP_Radial_D10.0mm_P5.00mm
D1, D2, D3: 1N4007; D_DO-41_SOD81_P10.16mm_Horizontal
D4: LED; LED_D5.0mm
J1, J2: Screw_Terminal_01x02; TerminalBlock_bornier-2_P5.08mm
Q1: TIP122; TO-220-3_Vertical
R1, R2: 1K; R_Axial_DIN0204_L3.6mm_D1.6mm_P7.62mm_Horizontal
R3: 2.2K; R_Axial_DIN0204_L3.6mm_D1.6mm_P7.62mm_Horizontal
RV1: 100K; Potentiometer_Alps_RK163_Single_Horizontal
U1: NE555P; DIP-8_W7.62mm

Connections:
GND: C1.2, C2.2, C3.2, D4.1 (K), J1.1, Q1.3 (E), U1.1 (GND)
unnamed: D1.2 (A), D2.1 (K), R1.2, U1.7 (DIS)
unnamed: D1.1 (K), RV1.3
unnamed: D2.2 (A), RV1.1
unnamed: D3.2 (A), J2.2, Q1.2 (C)
unnamed: C3.1, D3.1 (K), J1.2, J2.1, R1.1, R3.1, U1.4 (R), U1.8 (VCC)
unnamed: D4.2 (A), R3.2
unnamed: Q1.1 (B), R2.2
unnamed: C2.1, U1.5 (CV)
unnamed: R2.1, U1.3 (Q)
unnamed: C1.1, RV1.2, U1.2 (TR), U1.6 (THR)

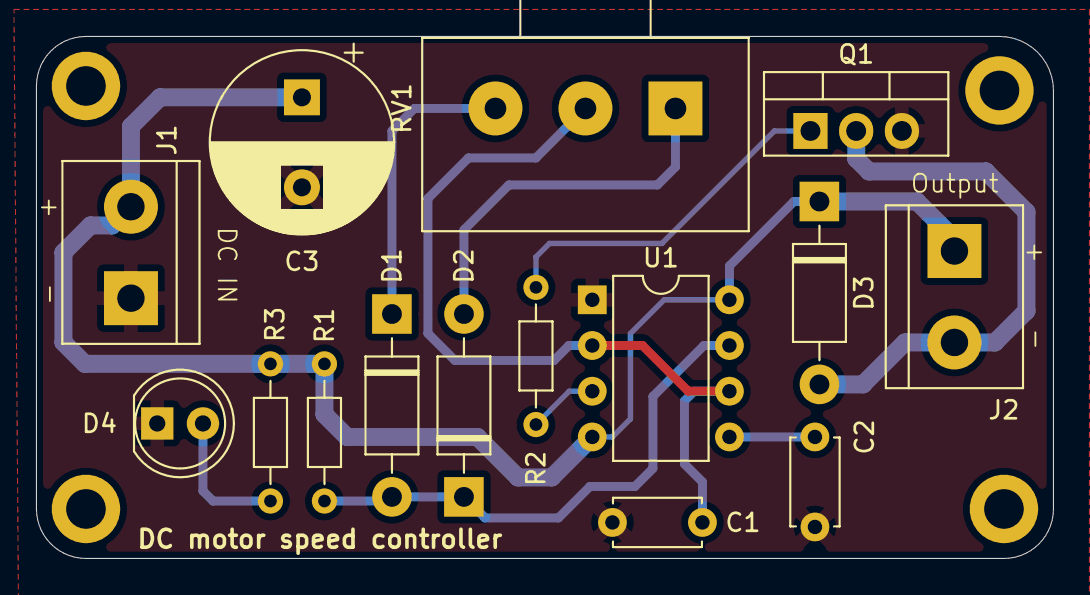
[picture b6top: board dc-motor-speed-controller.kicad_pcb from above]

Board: 2 copper layers, 56.5 x 29.0 mm, 15 parts (0 on the bottom side), 11 nets.
